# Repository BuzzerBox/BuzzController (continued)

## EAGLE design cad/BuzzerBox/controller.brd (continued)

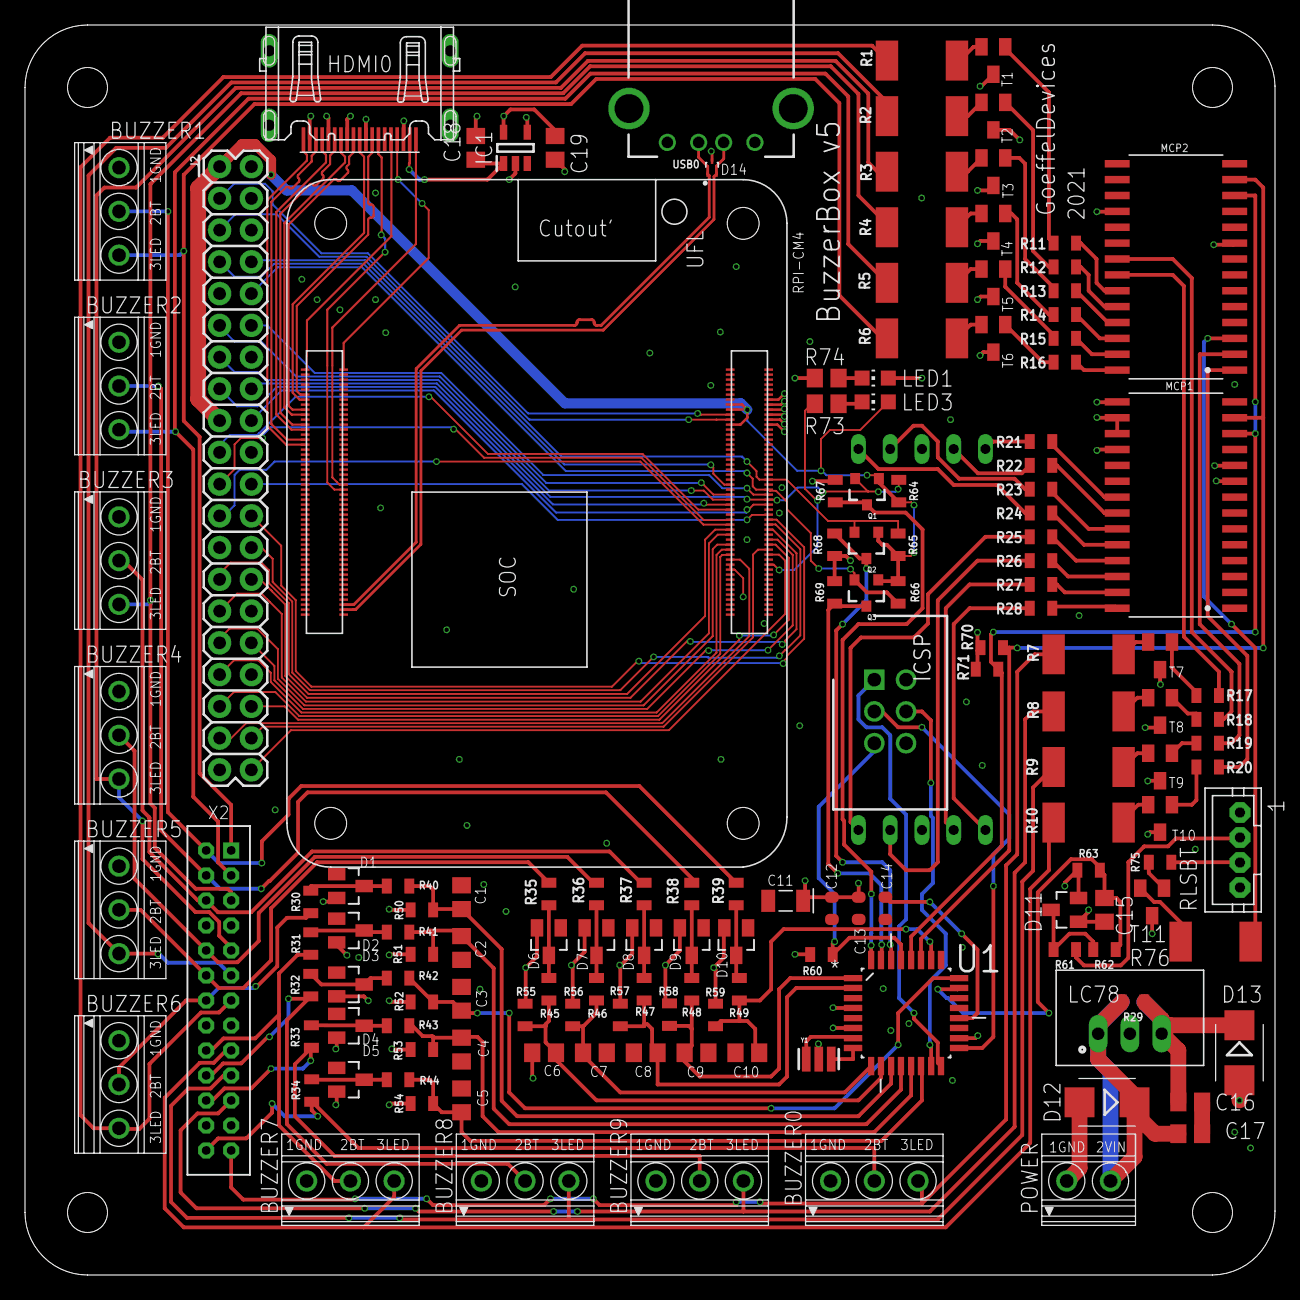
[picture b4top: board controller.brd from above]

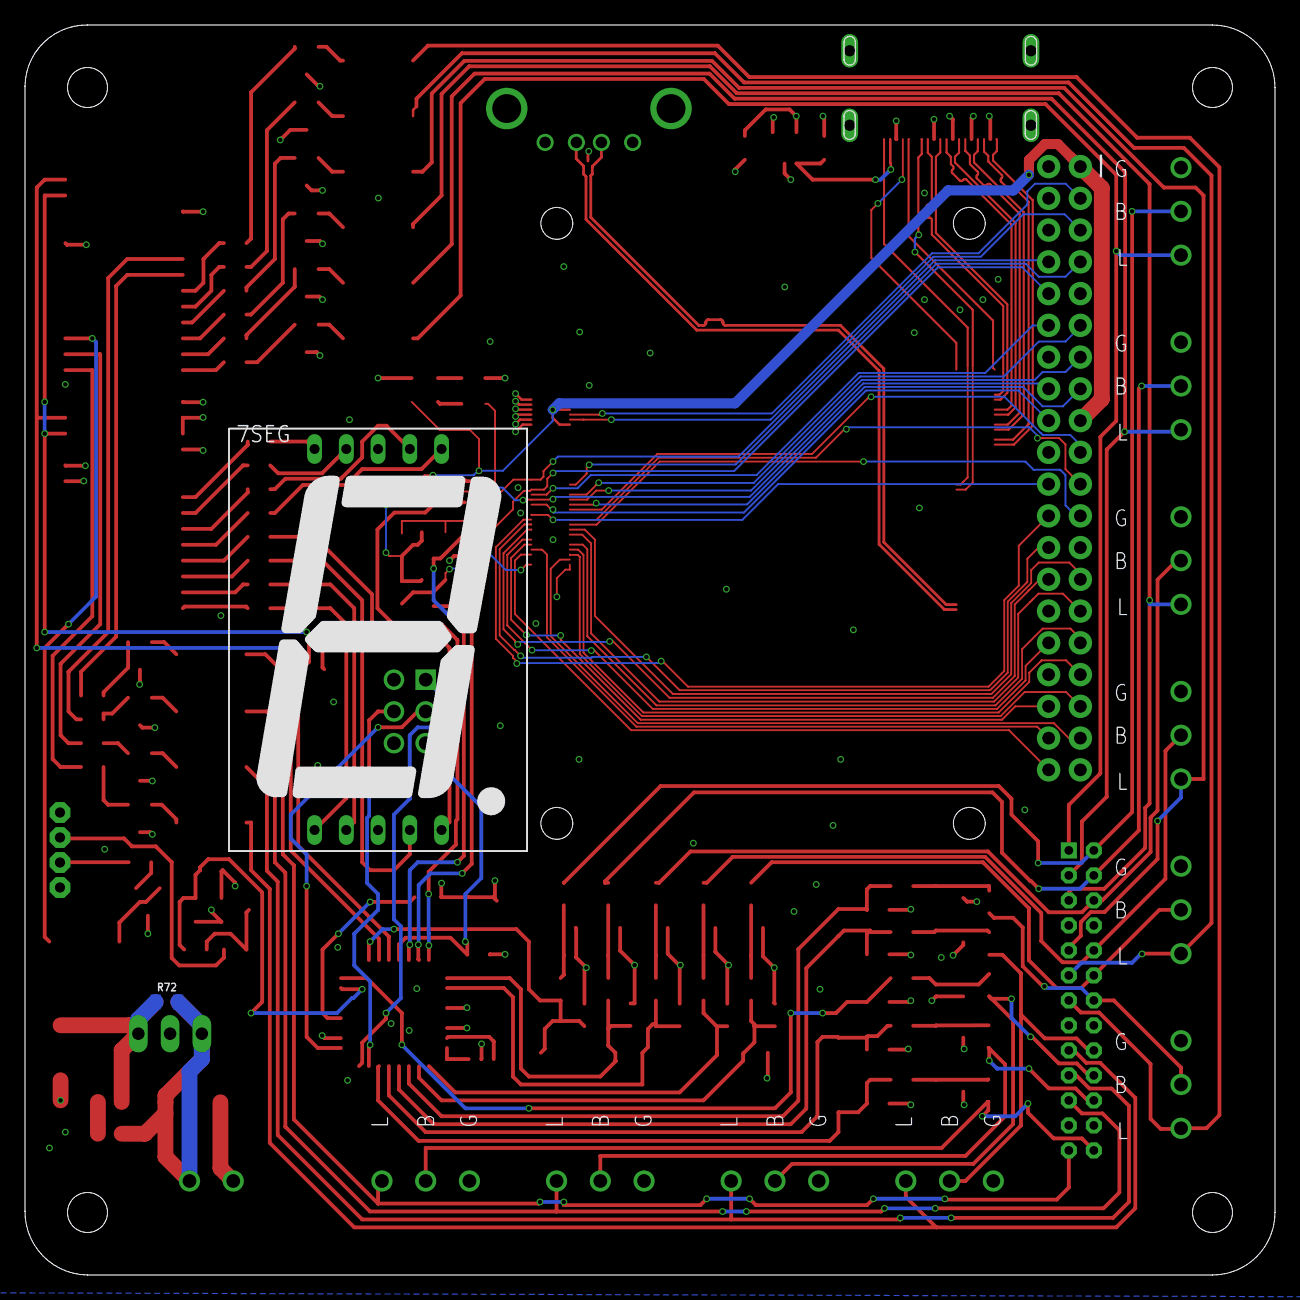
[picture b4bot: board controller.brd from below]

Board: 4 copper layers, 100.0 x 100.0 mm, 154 parts (2 on the bottom side), 155 nets.

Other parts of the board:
U$1, U$2, U$3, U$4: M3-HOLE

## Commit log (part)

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2021-05-09 Basic Button-Detection with Lock
2021-05-10 First draft PCB
2021-05-11 PCB V1
2021-05-20 Fix Boardlayout, Adapt code to Pro Micro
2021-05-23 Fix obvious pcb issues from V1
2021-05-24 Optimize Screw-Holes, postitions, pull back resist etc.
2021-05-28 Add 7-Segment-Display to Layout
2021-05-30 Add release button to board
2021-05-30 Added Pullup Resistors to I2C-Bus
2021-05-30 Clean up schematic
2021-05-31 Cleanup schematic
2021-05-31 Added transistors for more LED power
2021-05-31 Placed all transistors
2021-05-31 Reorganize Power-Supply, Add adjustment resistors to regulator
2021-06-02 Final Board V2
2021-06-03 Fix wrong silkscreen side for Buzzer connection ports
2021-06-04 Update resistor values for BOM
2021-06-05 Upgrade LED output resistors to bigger 2512 package to better handle larger currents
2021-06-09 Reposition components to keep similar components close together, for easier compoent placment
2021-06-10 Slight component rearangement
2021-06-10 Place all compoenents in logical groups for easy placement
2021-06-10 Move components closer together to create free space
2021-06-10 Replaced Arduino with bare uC
2021-06-10 Start adding the RPi CM4
2021-06-13 Add USB port
2021-06-18 Fix missig Reset pin voltage on I2c-expander
2021-06-18 Add helper functions to interact with 7-Segment display
2021-06-18 Consider basic button implementation
2021-06-19 Rearange Code
2021-06-19 Basic functions without RPi communication
2021-06-19 Add basic RPi communication
2021-06-20 Added Panel
2021-06-20 Basic Communication with RPi over Multimaster
2021-06-21 Added simple WDT
2021-06-21 Reorder Buzzers to match PCB-Silkscreen
2021-06-25 Add Side-Channel Signal line between uC and RPi
2021-06-25 Added HDMI
2021-06-25 Add pin header to support external PI
2021-06-25 Add slots to HDMI port
2021-06-26 Organize Sikscreen
2021-06-26 Length match differential paris
2021-06-26 Beef up power 5V power line
2021-06-26 Replace Arduino digitalRead with low level code
2021-06-26 Catch out ouf bound index via I2C
2021-06-26 Fix typo
2021-06-26 Connect necessary CM4 pins, according to documentation
2021-06-27 Ground HDMI chassis, add overvoltage protection
2021-06-27 Show 7Seg dot until request or command is received from Pi
2021-07-03 Check if lock is set
2021-07-04 Change state detection to new old method of keyboard input
2021-07-05 Changed to 4 layer stackup
2021-07-06 Route differential pairs for HDMI
2021-07-08 Completed 4 layer board
2021-07-08 Final Board V3
2021-07-08 Place cutout for antenna on all layers
2021-07-09 Pull back internal layers around non plated drill holes
2021-07-17 Fix HDMI pin offset
2021-08-05 Edge Detection for Release button
2021-08-05 Added missing trace
2021-08-06 Add level shifter for TX/RX
2021-08-06 Init ATmega 328p Config
2021-08-06 Change Buzzer trigger to interrupts
2021-08-07 Add input stage for Release button
2021-08-07 Replace fancy magic lookup table for buzzer identification with slower, but more reliable lookup
2021-08-07 Detect falling edege for release button
2021-08-08 Added serial communication with Pi
2021-08-09 Fix small pcb layout issues
2021-08-09 Start renaming resistors for better organization
2021-08-10 Relabel components
2021-08-10 Adjust Panel Layout. Remove Pi, Additional Screws. Add Supply. Rearange Power Inlet and Release Button
2021-08-17 Added combined header for buzzers
2021-08-18 Add Dc-Dc Circuit, for possible 12V supply
2021-08-19 Reduce connector pitch to 2mm for XLR-Board-Connection
2021-08-19 Reduce connector pitch to 2mm for Release button
2021-08-19 Move buzzer pcb connector away from GPIO Header
2021-08-19 Add XLR-TOP-PCB
2021-08-20 Added leds
2021-08-20 Changed keepout etc for xlr connectors.
2021-09-01 Change XLR PCB to equal spacing
2021-09-01 Change Spacing on panel
2021-09-05 Change to 3 byte messages
2021-09-05 Added ESD protection to USB
2021-09-06 Move to PlatformIO
2021-09-06 Remove old File structure
2021-09-06 Reorganize communication classes
2021-09-07 Improve locial separation in classes
2021-09-07 Disable WDT
2021-09-07 Enable WDT, Fix endless loop
2021-09-07 Implemented Rpi-Connection Heartbeat
2021-09-07 Handle incoming Serial resiliently against missing or added bytes
2021-09-09 Rearrange BuzzerIDs for new PCB-Layout
2021-09-11 Added PE to XLR Board
2021-09-24 V3 XLRBoard
2021-10-16 Add DevKeys
2021-11-04 Add TTL Adapter for Devkit
2026-03-20 Udpate Readme
2026-03-22 Attempt to fix selection change after locking bug
2026-03-22 Add software debounce. Closes #10
